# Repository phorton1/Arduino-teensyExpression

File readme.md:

# teensyExpression MIDI controller

This github repository describes and contains the source code and other materials
for a 3D printed, **teensy 3.6** based MIDI controller.  The controller has a 5x5 array
of switches, each with an individually adressable ws2812B colored LED,
four rotary controllers,
a 3.5" touchscreen,
inputs for four (4) standard 1/4" expression pedals, a 1/8" stereo jack used for a serial port, and the main USB type "A" connector,
a USB host port, and, lol, a volt/amp meter to monitor the USB power supply.

*four rotary controllers*

*3.5" touchscreen*

*inputs for four (4) standard 1/4" expression pedals, 1/8" stereo jack for serial port, and the main USB type "A" connector*

*USB host port, and volt/amp meter on USB power supply*

It is intended to be a *foot* controller ... hence the tiered setup which makes it
easier to press buttons with your toes without having to reach over other buttons.
FWIW, I play the guitar barefooted, while sitting in a chair.

There are two major aspects to this project.  First there is the [**hardware**](hardware/), which is
relatively straight forward, and there are circuit diagrams, fusion 360 files, some
instructions, and so on that might allow someone to create a copy if they wanted to.

The second major aspect is the [**software**](design/). Inasmuch as this was conceived as BOTH an
experimental platform to let me mess with USB midi, and particularly the **Fishman FTP
Triple Play** dongle/controller, it also has been programmed to fit into my existing
performance setup.  For me, it is "gig ready", as well as a place I can try different
experiments with various things.

The software does not present itself as a general purpose, commercially viable,
consumer product.  Though that could be done, it is not my primary focus. So, while
I would be able to create, for example, a box on which the end user could map the
buttons to various MIDI CC control messages at "run time", that is not currently
implemented.

Because the entire thing can be (fairly) easily programmed from the Arduino IDE,
at this time I am selfishly doing whatever the heck I want in C++.   Some stuff
has been modularized and incorporated into things like a system configuration "preferences"
page, with persistent values stored in EEPROM, other stuff is "hard coded" into the C++, an
approach which limits the use of this by less technically saavy "consumer" or "nubie"
readers and potential users.

That's what it is.

There is still, in my opinion, considerable value in making this public, and so,
here, in spite of ongoing development, I am creating a public github
repository so that I can present it to you.

## THIS Repository Organization

The following subfolders are considered "public":

* [teensyExpression/](teensyExpression/) - contains the C++ source code,
  including the main INO file (teensyExpression.ino) and the C++ and H files
  needed to build the program.
* [design/](design/) - contains a description of the software architecture,
  with ideas on how other programmers might extend it, along with a
  description of the [User Interface](design/readme_ui.md) in it's
  current incarnation, including the [songMachine](design/readme_songmachine.md)
* [hardware/](hardware/) - contains the basic schematic, circuit diagrams,
  and information about building the electronics portion of the project.
* [ftp/](ftp/) - contains separate discussions and documents regarding
   my reverse engineering efforts on the FTP Triple Play dongle and controller

There are a number of other sub-folders which are considered "private" for my own
personal use, and/or which exist only to support the readme.md files in the this
and the above subfolders:

* **images** - contains images used on this and various readme pages
* **junk** - contains a variety of weird files, images, doc files, that, for me, pertain
      to the design of the project, but which are not meant to be necessrily useful
      for a reader or anyone besides myself.
* **tests** - contains a number of test programs that are not necessarily currently up-to-date
    or useful.  I keep these for posterities sake as they may have snippets of code I will
    need in the future.

### 3D Printing Information

There is a separate repository containing the Fusion 360, STL, and gcode files
for this project that were used to 3D print the box and buttons.

* [fusion/](https://github.com/phorton1/Arduino-teensyExpression-fusion) - contains the STL, fusion 360 files, and notes on how to print and assemble the box

### Please See

This teensyExpression pedal is intimately involved with my long term ongoing
**[rPi bare metal vGuitar rig](https://hackaday.io/project/165696-rpi-bare-metal-vguitar-rig)**
project at hackaday.

In that process I have developed a number of other repositories which might be of interest
to audio system development hackers, including:

* **[circle](https://github.com/phorton1/circle)** - my fork of a a C++ bare metal rPi
development framework
* **[circle-prh](https://github.com/phorton1/circle-prh)** - my extensions to Circle, including
a port of the **Teensy Audio Library** to rPi bare metal, and an Arduino like development
approach.
* **[Loooper](https://github.com/phorton1/circle-prh-apps-Looper)** - a bare metal rPi based **Audio Looper**
including a 3D printed case with a 7" touchscreen, which hooks up to, and is controlled by,
this teensyExpression pedal.

### Notes on Building and GitHub **DEPENDENCIES**

This project relies on the teensyDuino installation.

It also depends on a number of Arduino libraries that must be manually placed in your
Arduino/libraries folder.  There is one small library that I wrote (myDebug.h and myDebug.cpp),
that I generally use in my Arduino programs, and is common to more than one of my published projects.

In addition there are several libraries that are publicly available, but unchanged by me
(ILI9341_t3 and ILI9341_fonts), which I have forked into my github account for ease in finding them,
and to provide me with a stable known "snapshot" of those libraries.

And finally there are some libraries that are publicly available, but to which I
have made modifications to, small or large, in order to get them to work in this project
(Paul's USBHost_t36 and my_LCDWIKI_*).

Each of these libraries is available as a github project here in my account, with a
name that is formatted like "Arduino-libraries-NameOfLibrary".   **These libraries
should be "cloned" or otherwise copied into your Arduino/libraries folder**.  Once
you have done that, you may rename them to remove the "Arduino-libraries" portion,
just leaving the NameOfLibrary portion in the directory structure if you wish.

* [myDebug](https://github.com/phorton1/Arduino-libraries-myDebug) -
   A debugging output library common to my Arduino projects, it contains
   global methods with names like "display" and "display_bytes" which are called
   throughout my code, and which can be turned on or off via defines.

* [base64](https://github.com/phorton1/Arduino-libraries-base64) -
  UNMODIFIED fork of Adam Rudd's https://github.com/adamvr/arduino-base64 repository

* [ILI9341_t3](https://github.com/phorton1/Arduino-libraries-ILI9341_t3) and
  [ILI9341_fonts](https://github.com/phorton1/Arduino-libraries-ILI9341_fonts) -
  These are UNMODIFIED versions of Paul's ILI9341 libraries, forked from
  his repository on 2020-10-03.   My program *may* compile and work with
  more current versions that he makes available at https://github.com/PaulStoffregen/ILI9341_t3
  and https://github.com/PaulStoffregen/ILI9341_fonts, but these forks are
  known to compile and work properly with my code.

* [USBHost_t36](https://github.com/phorton1/Arduino-libraries-USBHost_t36) -
  A slightly MODIFIED version of Paul's USBHost_t36 library, forked
  from https://github.com/PaulStoffregen/USBHost_t36 on 2020-10-03.
  The API was changed to make a few functions virtual and to expose
  a few private variables as "protected".

* [SdFat](https://github.com/phorton1/Arduino-libraries-SdFat) -
  A fork of Bill Greiman's https://github.com/greiman/SdFat with one slight
  modification - to increase BUSY_TIMEOUT_MICROS from 500000 to 1000000,
  which fixed problems I was having opening an SD card on a fresh boot.

* [my_LCDWIKI_GUI](https://github.com/phorton1/Arduino-libraries-my_LCDWIKI_GUI),
  [my_LCDWIKI_KBV](https://github.com/phorton1/Arduino-libraries-my_LCDWIKI_KBV), and
  [my_LCDWIKI_TouchScreen](https://github.com/phorton1/Arduino-libraries-my_LCDWIKI_TouchScreen) -
  These repositories contain the rude and crude port of the LCDWIKI Arduino libraries
  to the Teensy for the cheap touch screen I ended up using.  The touch screen
  is an 8 bit parellel port screen that looks like this:

When I started working on this project, I started off using a different, much
faster and more teensy compatible 2.8" SPI touch screen.  One night I burned it, and
because I did not want to wait 6 weeks for a replacement (I live on a remote
island in the tropics) I was forced to go to a slower speed 8 bit parallel
Arduino touch screen ... which in turn required me to port the LCDWIKI library
for it to the teensy 3.6, which I did.

# Credits

Pretty much everything I do has been tremendously influenced by, and is more or less a direct
result of the work done by **Paul Stoffregen** and his wonderful **teensy** series of MPU boards.

Please visit his website at [prjc.com](https://www.prjc.com) and support him by purchasing teensy
boards and teensy related parts and accessories.    He also has github, hackaday, and facebook pages
that you can find easily on the internet. The man's a giant to me, and has forged important new
ground not only with the boards he makes, but also with the **vast** amount of open source
software he has created, not the least of which includes the ws2812 and ili9431 libraries, but
also his audio library, and well, what can you say ... so much more!

Also thanks to the many folks who have contributed to the [lcdwiki](http://www.lcdwiki.com) project.
Though I can't name them by name, many are the times when I have visited their website and utilized
their code.

That's it!

Thanks for checking this out!

Updated October 2020 - Patrick

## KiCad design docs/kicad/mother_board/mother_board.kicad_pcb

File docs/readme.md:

# teensyExpression MIDI controller

This github repository describes and contains the source code and other materials
for a 3D printed, **teensy 3.6** based MIDI controller.  The controller has a 5x5 array
of switches, each with an individually adressable ws2812B colored LED,
four rotary controllers,
a 3.5" touchscreen,
inputs for four (4) standard 1/4" expression pedals, a 1/8" stereo jack used for a serial port, and the main USB type "A" connector,
a USB host port, and, lol, a volt/amp meter to monitor the USB power supply.

*four rotary controllers*

*3.5" touchscreen*

*inputs for four (4) standard 1/4" expression pedals, 1/8" stereo jack for serial port, and the main USB type "A" connector*

*USB host port, and volt/amp meter on USB power supply*

It is intended to be a *foot* controller ... hence the tiered setup which makes it
easier to press buttons with your toes without having to reach over other buttons.
FWIW, I play the guitar barefooted, while sitting in a chair.

There are two major aspects to this project.  First there is the [**hardware**](hardware.md), which is
relatively straight forward, and there are circuit diagrams, fusion 360 files, some
instructions, and so on that might allow someone to create a copy if they wanted to.

The second major aspect is the [**software**](design.md). Inasmuch as this was conceived as BOTH an
experimental platform to let me mess with USB midi, and particularly the **Fishman FTP
Triple Play** dongle/controller, it also has been programmed to fit into my existing
performance setup.  For me, it is "gig ready", as well as a place I can try different
experiments with various things.

The software does not present itself as a general purpose, commercially viable,
consumer product.  Though that could be done, it is not my primary focus. So, while
I would be able to create, for example, a box on which the end user could map the
buttons to various MIDI CC control messages at "run time", that is not currently
implemented.

Because the entire thing can be (fairly) easily programmed from the Arduino IDE,
at this time I am selfishly doing whatever the heck I want in C++.   Some stuff
has been modularized and incorporated into things like a system configuration "preferences"
page, with persistent values stored in EEPROM, other stuff is "hard coded" into the C++, an
approach which limits the use of this by less technically saavy "consumer" or "nubie"
readers and potential users.

That's what it is.

There is still, in my opinion, considerable value in making this public, and so,
here, in spite of ongoing development, I am creating a public github
repository so that I can present it to you.

## THIS Repository Organization

TODO: rework this whole section

This repository contains the C++ source code,
  including the main INO file (teensyExpression.ino) and the C++ and H files
  needed to build the program.

There are a number of other sub-folders which are considered "private" for my own
personal use, and/or which exist only to support the readme.md files in the this
and the above subfolders:

* **images** - contains images used on this and various readme pages
* **junk** - contains a variety of weird files, images, doc files, that, for me, pertain
      to the design of the project, but which are not meant to be necessrily useful
      for a reader or anyone besides myself.
* **tests** - contains a number of test programs that are not necessarily currently up-to-date
    or useful.  I keep these for posterities sake as they may have snippets of code I will
    need in the future.

### 3D Printing Information

There is a separate repository containing the Fusion 360, STL, and gcode files
for this project that were used to 3D print the box and buttons.

TODO: rework

### Please See

This teensyExpression pedal is intimately involved with my long term ongoing
**[rPi bare metal vGuitar rig](https://hackaday.io/project/165696-rpi-bare-metal-vguitar-rig)**
project at hackaday.

In that process I have developed a number of other repositories which might be of interest
to audio system development hackers, including:

* **[circle](https://github.com/phorton1/circle)** - my fork of a a C++ bare metal rPi
development framework
* **[circle-prh](https://github.com/phorton1/circle-prh)** - my extensions to Circle, including
a port of the **Teensy Audio Library** to rPi bare metal, and an Arduino like development
approach.
* **[Loooper](https://github.com/phorton1/circle-prh-apps-Looper)** - a bare metal rPi based **Audio Looper**
including a 3D printed case with a 7" touchscreen, which hooks up to, and is controlled by,
this teensyExpression pedal.

### Notes on Building and GitHub **DEPENDENCIES**

This project relies on the teensyDuino installation.

It also depends on a number of Arduino libraries that must be manually placed in your
Arduino/libraries folder.  There is one small library that I wrote (myDebug.h and myDebug.cpp),
that I generally use in my Arduino programs, and is common to more than one of my published projects.

In addition there are several libraries that are publicly available, but unchanged by me
(ILI9341_t3 and ILI9341_fonts), which I have forked into my github account for ease in finding them,
and to provide me with a stable known "snapshot" of those libraries.

And finally there are some libraries that are publicly available, but to which I
have made modifications to, small or large, in order to get them to work in this project
(Paul's USBHost_t36 and my_LCDWIKI_*).

Each of these libraries is available as a github project here in my account, with a
name that is formatted like "Arduino-libraries-NameOfLibrary".   **These libraries
should be "cloned" or otherwise copied into your Arduino/libraries folder**.  Once
you have done that, you may rename them to remove the "Arduino-libraries" portion,
just leaving the NameOfLibrary portion in the directory structure if you wish.

* [myDebug](https://github.com/phorton1/Arduino-libraries-myDebug) -
   A debugging output library common to my Arduino projects, it contains
   global methods with names like "display" and "display_bytes" which are called
   throughout my code, and which can be turned on or off via defines.

TODO: cleanup NEEDS vs USES forked libraries

* **base64** -
  UNMODIFIED fork of Adam Rudd's https://github.com/adamvr/arduino-base64 repository
* [ILI9341_t3](https://github.com/phorton1/Arduino-libraries-ILI9341_t3) and
  [ILI9341_fonts](https://github.com/phorton1/Arduino-libraries-ILI9341_fonts) -
  These are UNMODIFIED versions of Paul's ILI9341 libraries, forked from
  his repository on 2020-10-03.   My program *may* compile and work with
  more current versions that he makes available at https://github.com/PaulStoffregen/ILI9341_t3
  and https://github.com/PaulStoffregen/ILI9341_fonts, but these forks are
  known to compile and work properly with my code.

* [USBHost_t36](https://github.com/phorton1/Arduino-libraries-USBHost_t36) -
  A slightly MODIFIED version of Paul's USBHost_t36 library, forked
  from https://github.com/PaulStoffregen/USBHost_t36 on 2020-10-03.
  The API was changed to make a few functions virtual and to expose
  a few private variables as "protected".

* [SdFat](https://github.com/phorton1/Arduino-libraries-SdFat) -
  A fork of Bill Greiman's https://github.com/greiman/SdFat with one slight
  modification - to increase BUSY_TIMEOUT_MICROS from 500000 to 1000000,
  which fixed problems I was having opening an SD card on a fresh boot.

* [my_LCDWIKI_GUI](https://github.com/phorton1/Arduino-libraries-my_LCDWIKI_GUI),
  [my_LCDWIKI_KBV](https://github.com/phorton1/Arduino-libraries-my_LCDWIKI_KBV), and
  [my_LCDWIKI_TouchScreen](https://github.com/phorton1/Arduino-libraries-my_LCDWIKI_TouchScreen) -
  These repositories contain the rude and crude port of the LCDWIKI Arduino libraries
  to the Teensy for the cheap touch screen I ended up using.  The touch screen
  is an 8 bit parellel port screen that looks like this:

When I started working on this project, I started off using a different, much
faster and more teensy compatible 2.8" SPI touch screen.  One night I burned it, and
because I did not want to wait 6 weeks for a replacement (I live on a remote
island in the tropics) I was forced to go to a slower speed 8 bit parallel
Arduino touch screen ... which in turn required me to port the LCDWIKI library
for it to the teensy 3.6, which I did.

# Credits

Pretty much everything I do has been tremendously influenced by, and is more or less a direct
result of the work done by **Paul Stoffregen** and his wonderful **teensy** series of MPU boards.

Please visit his website at [prjc.com](https://www.prjc.com) and support him by purchasing teensy
boards and teensy related parts and accessories.    He also has github, hackaday, and facebook pages
that you can find easily on the internet. The man's a giant to me, and has forged important new
ground not only with the boards he makes, but also with the **vast** amount of open source
software he has created, not the least of which includes the ws2812 and ili9431 libraries, but
also his audio library, and well, what can you say ... so much more!

Also thanks to the many folks who have contributed to the [lcdwiki](http://www.lcdwiki.com) project.
Though I can't name them by name, many are the times when I have visited their website and utilized
their code.

That's it!

Thanks for checking this out!

Updated October 2020 - Patrick

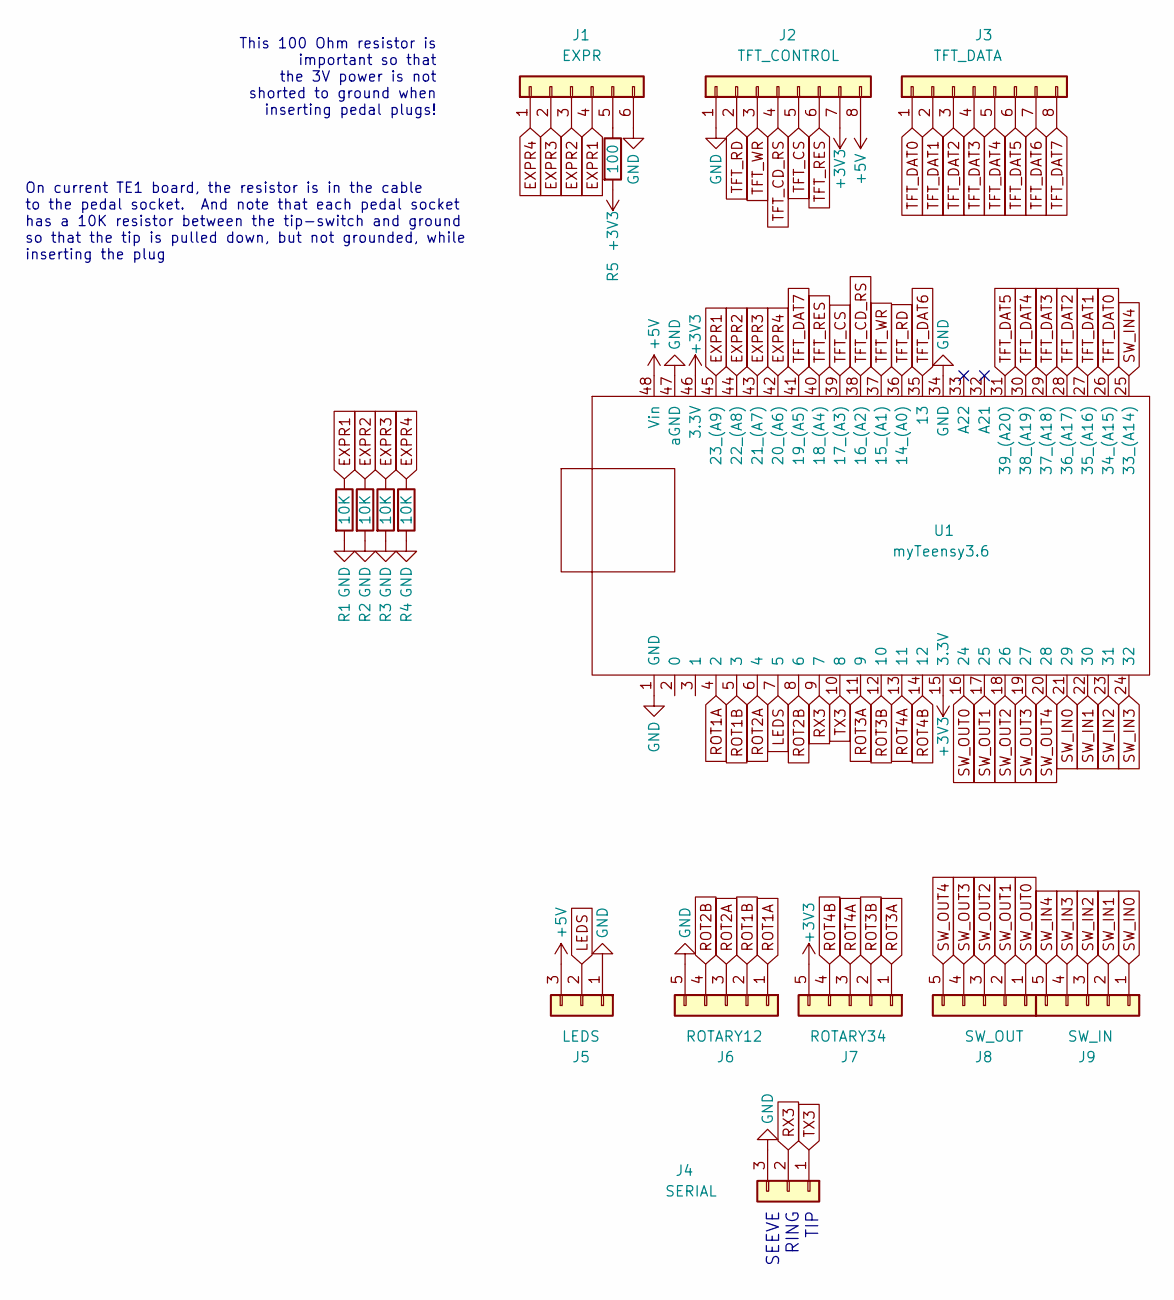
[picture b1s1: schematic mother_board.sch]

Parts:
J1: EXPR; myPinSocket_1x06
J2: TFT_CONTROL; myJSTx08
J3: TFT_DATA; myJSTx08
J4: SERIAL; myPinSocket_1x03
J5: LEDS; myPinSocket_1x03
J6: ROTARY12; myPinSocket_1x05
J7: ROTARY34; myPinSocket_1x05
J8: SW_OUT; myPinSocket_1x05
J9: SW_IN; myPinSocket_1x05
R1, R2, R3, R4: 10K; myResistor
R5: 100; myResistor
U1: myTeensy3.6

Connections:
+3V3: J2.7, J7.5, R5.2, U1.15 (3.3V), U1.46 (3.3V)
+5V: J2.8, J5.3, U1.48 (Vin)
EXPR1: J1.4, R1.1, U1.45 (23_(A9))
EXPR2: J1.3, R2.1, U1.44 (22_(A8))
EXPR3: J1.2, R3.1, U1.43 (21_(A7))
EXPR4: J1.1, R4.1, U1.42 (20_(A6))
GND: J1.6, J2.1, J4.3, J5.1, J6.5, R1.2, R2.2, R3.2, R4.2, U1.1 (GND), U1.34 (GND), U1.47 (aGND)
LEDS: J5.2, U1.7 (5)
unnamed: J1.5, R5.1
ROT1A: J6.1, U1.4 (2)
ROT1B: J6.2, U1.5 (3)
ROT2A: J6.3, U1.6 (4)
ROT2B: J6.4, U1.8 (6)
ROT3A: J7.1, U1.11 (9)
ROT3B: J7.2, U1.12 (10)
ROT4A: J7.3, U1.13 (11)
ROT4B: J7.4, U1.14 (12)
RX3: J4.2, U1.9 (7)
SW_IN0: J9.1, U1.21 (29)
SW_IN1: J9.2, U1.22 (30)
SW_IN2: J9.3, U1.23 (31)
SW_IN3: J9.4, U1.24 (32)
SW_IN4: J9.5, U1.25 (33_(A14))
SW_OUT0: J8.1, U1.16 (24)
SW_OUT1: J8.2, U1.17 (25)
SW_OUT2: J8.3, U1.18 (26)
SW_OUT3: J8.4, U1.19 (27)
SW_OUT4: J8.5, U1.20 (28)
TFT_CD_RS: J2.4, U1.38 (16_(A2))
TFT_CS: J2.5, U1.39 (17_(A3))
TFT_DAT0: J3.1, U1.26 (34_(A15))
TFT_DAT1: J3.2, U1.27 (35_(A16))
TFT_DAT2: J3.3, U1.28 (36_(A17))
TFT_DAT3: J3.4, U1.29 (37_(A18))
TFT_DAT4: J3.5, U1.30 (38_(A19))
TFT_DAT5: J3.6, U1.31 (39_(A20))
TFT_DAT6: J3.7, U1.35 (13)
TFT_DAT7: J3.8, U1.41 (19_(A5))
TFT_RD: J2.2, U1.36 (14_(A0))
TFT_RES: J2.6, U1.40 (18_(A4))
TFT_WR: J2.3, U1.37 (15_(A1))
TX3: J4.1, U1.10 (8)

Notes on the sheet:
SEEVE RING TIP
This 100 Ohm resistor is important so that the 3V power is not shorted to ground when inserting pedal plugs!
On current TE1 board, the resistor is in the cable to the pedal socket. And note that each pedal socket has a 10K resistor between the tip-switch and ground so that the tip is pulled down, but not grounded, while inserting the plug

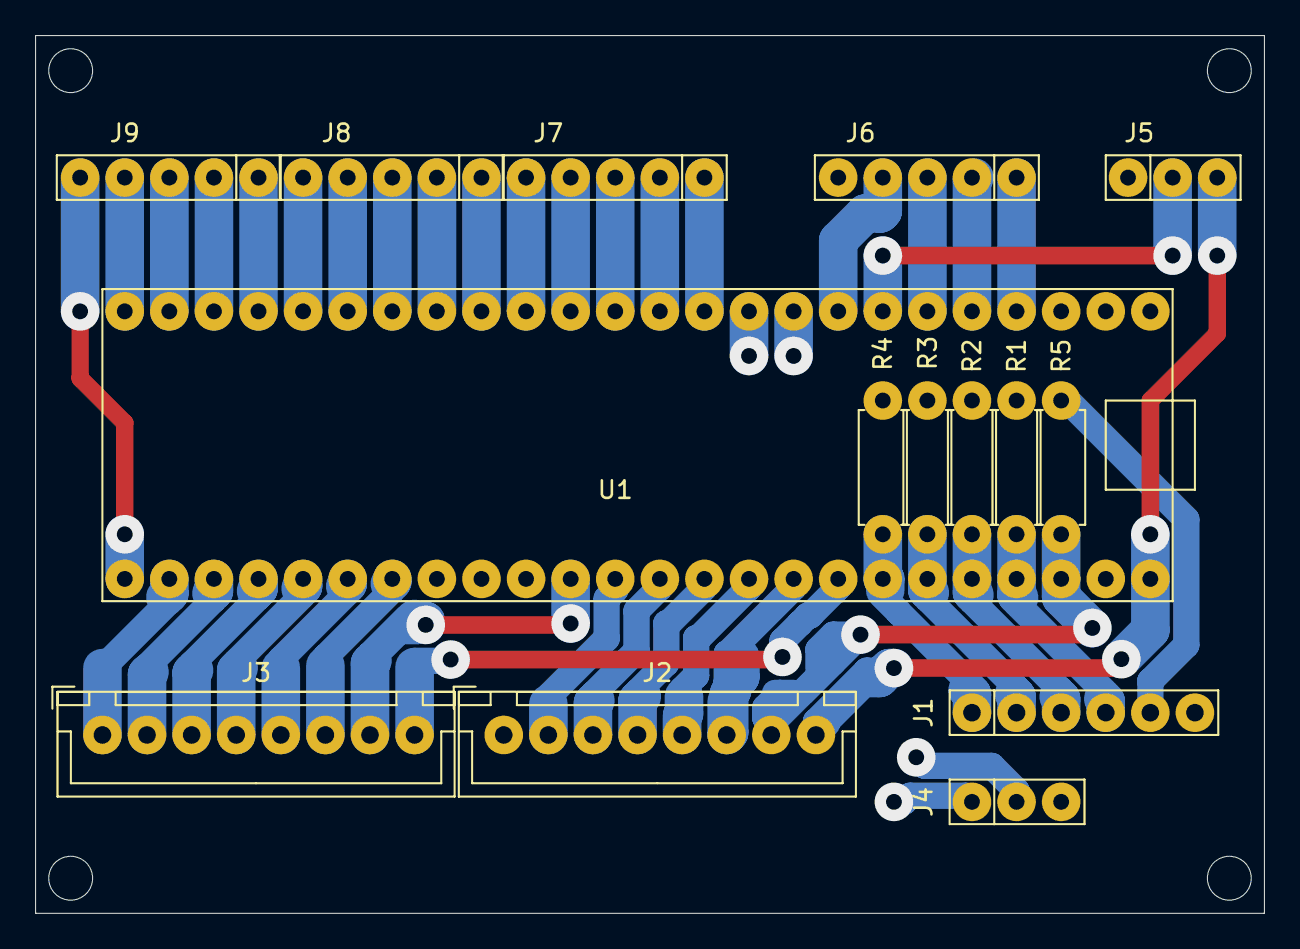
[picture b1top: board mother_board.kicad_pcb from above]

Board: 2 copper layers, 70.0 x 50.0 mm, 15 parts (0 on the bottom side), 42 nets.

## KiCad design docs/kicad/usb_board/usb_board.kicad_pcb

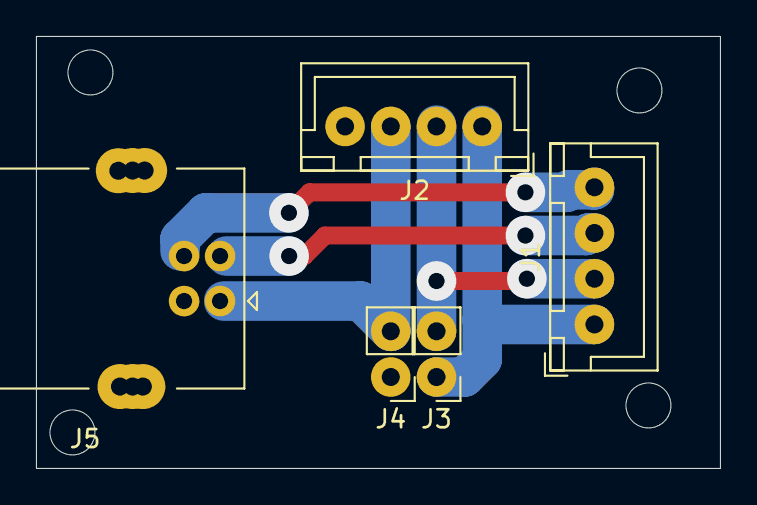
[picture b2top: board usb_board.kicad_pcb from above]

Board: 2 copper layers, 38.0 x 24.0 mm, 5 parts (0 on the bottom side), 6 nets.

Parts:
J1: USB_OUT; myJSTx04
J2: PWR_IO; myJSTx04
J3: JUMP_OUT; myPinHeader_1x02
J4: JUMP_IN; myPinHeader_1x02
J5: myUSB_B_Socket

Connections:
+5V: J2.3, J4.2, J5.1
D+: J1.4, J5.3
D-: J1.3, J5.2
GND: J2.4, J4.1, J5.4
unnamed: J1.1, J2.1, J3.1
unnamed: J1.2, J2.2, J3.2

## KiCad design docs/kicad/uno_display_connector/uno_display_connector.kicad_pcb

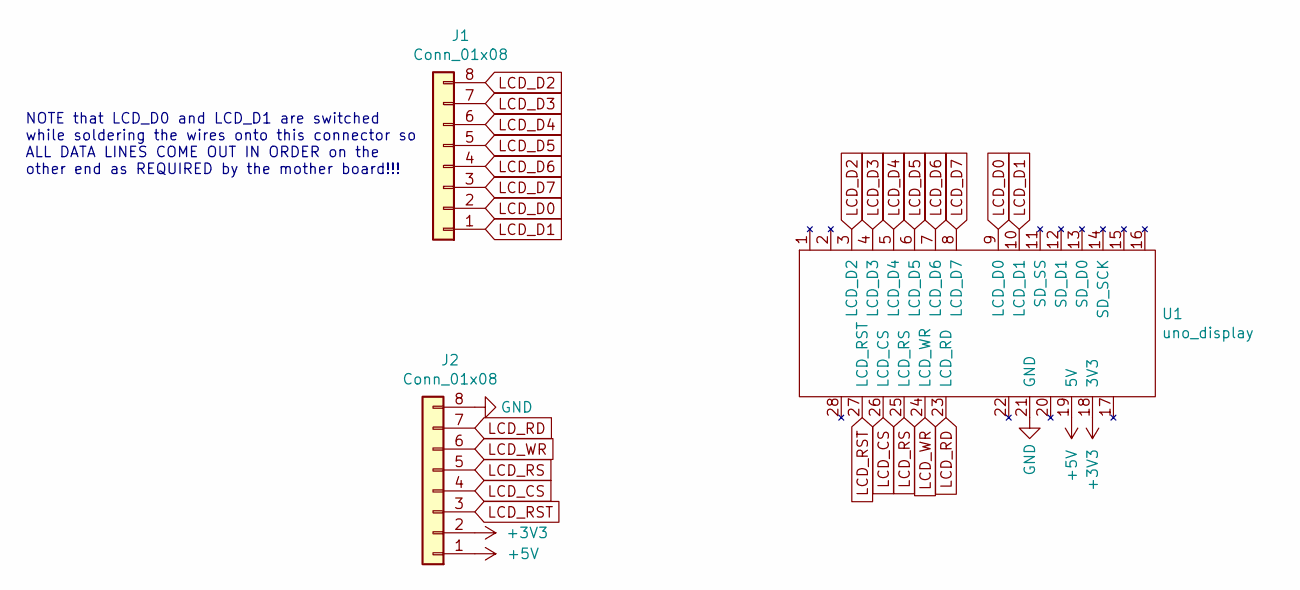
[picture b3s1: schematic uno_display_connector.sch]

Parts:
J1, J2: Conn_01x08; my8Pin
U1: uno_display; unoDisplay

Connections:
+3V3: J2.2, U1.18 (3V3)
+5V: J2.1, U1.19 (5V)
GND: J2.8, U1.21 (GND)
LCD_CS: J2.4, U1.26 (LCD_CS)
LCD_D0: J1.2, U1.9 (LCD_D0)
LCD_D1: J1.1, U1.10 (LCD_D1)
LCD_D2: J1.8, U1.3 (LCD_D2)
LCD_D3: J1.7, U1.4 (LCD_D3)
LCD_D4: J1.6, U1.5 (LCD_D4)
LCD_D5: J1.5, U1.6 (LCD_D5)
LCD_D6: J1.4, U1.7 (LCD_D6)
LCD_D7: J1.3, U1.8 (LCD_D7)
LCD_RD: J2.7, U1.23 (LCD_RD)
LCD_RS: J2.5, U1.25 (LCD_RS)
LCD_RST: J2.3, U1.27 (LCD_RST)
LCD_WR: J2.6, U1.24 (LCD_WR)

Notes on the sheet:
NOTE that LCD_D0 and LCD_D1 are switched while soldering the wires onto this connector so ALL DATA LINES COME OUT IN ORDER on the other end as REQUIRED by the mother board!!!

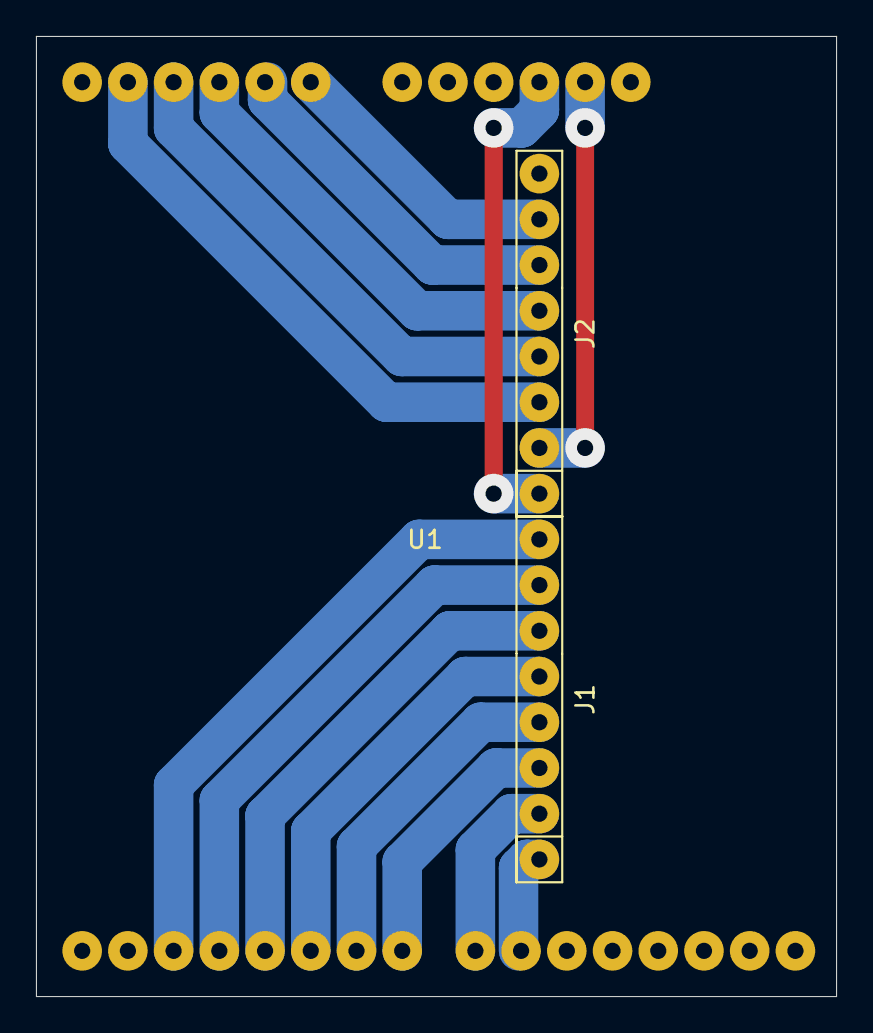
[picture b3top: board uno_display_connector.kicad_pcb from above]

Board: 2 copper layers, 44.5 x 53.3 mm, 3 parts (0 on the bottom side), 16 nets.

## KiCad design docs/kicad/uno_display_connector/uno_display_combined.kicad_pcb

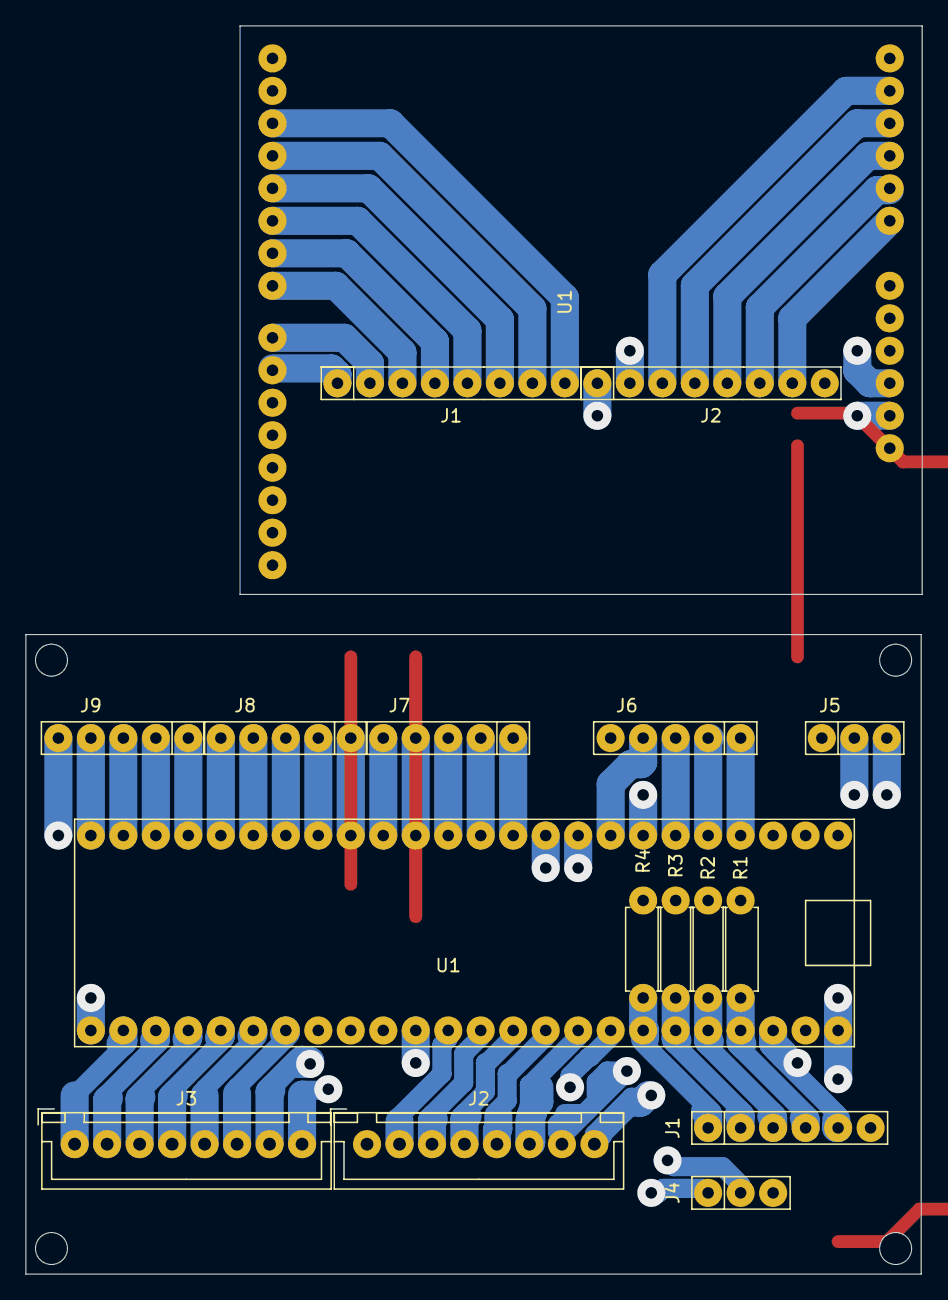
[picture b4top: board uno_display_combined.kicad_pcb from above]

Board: 2 copper layers, 70.0 x 50.0 mm, 17 parts (0 on the bottom side), 55 nets.

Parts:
J1: EXPR; myPinSocket_1x06
J1#2, J2: Conn_01x08; my8Pin
J2#2: TFT_CONTROL; myJSTx08
J3: TFT_DATA; myJSTx08
J4: SERIAL; myPinSocket_1x03
J5: LEDS; myPinSocket_1x03
J6: ROTARY12; myPinSocket_1x05
J7: ROTARY34; myPinSocket_1x05
J8: SW_OUT; myPinSocket_1x05
J9: SW_IN; myPinSocket_1x05
R1, R2, R3, R4: 10K; myResistor
U1: uno_display; unoDisplay
U1#2: myTeensy3.6

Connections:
+3V3: J1.5, J2.1, J2#2.7, J7.5, U1.18, U1#2.15, U1#2.46
+5V: J2.2, J2#2.8, J5.3, U1.19, U1#2.48
EXPR1: J1.4, R1.1, U1#2.45
EXPR2: J1.3, R2.1, U1#2.44
EXPR3: J1.2, R3.1, U1#2.43
EXPR4: J1.1, R4.1, U1#2.42
GND: J1.6, J2.8, J2#2.1, J4.3, J5.1, J6.5, R1.2, R2.2, R3.2, R4.2, U1.21, U1#2.1, U1#2.34, U1#2.47
LCD_CS: J2.4, U1.26
LCD_D0: J1#2.2, U1.9
LCD_D1: J1#2.1, U1.10
LCD_D2: J1#2.8, U1.3
LCD_D3: J1#2.7, U1.4
LCD_D4: J1#2.6, U1.5
LCD_D5: J1#2.5, U1.6
LCD_D6: J1#2.4, U1.7
LCD_D7: J1#2.3, U1.8
LCD_RD: J2.7, U1.23
LCD_RS: J2.5, U1.25
LCD_RST: J2.3, U1.27
LCD_WR: J2.6, U1.24
LEDS: J5.2, U1#2.7
unnamed: U1.2, U1#2.2
ROT1A: J6.1, U1#2.4
ROT1B: J6.2, U1#2.5
ROT2A: J6.3, U1#2.6
ROT2B: J6.4, U1#2.8
ROT3A: J7.1, U1#2.11
ROT3B: J7.2, U1#2.12
ROT4A: J7.3, U1#2.13
ROT4B: J7.4, U1#2.14
RX3: J4.2, U1#2.9
SW_IN0: J9.1, U1#2.21
SW_IN1: J9.2, U1#2.22
SW_IN2: J9.3, U1#2.23
SW_IN3: J9.4, U1#2.24
SW_IN4: J9.5, U1#2.25
SW_OUT0: J8.1, U1#2.16
SW_OUT1: J8.2, U1#2.17
SW_OUT2: J8.3, U1#2.18
SW_OUT3: J8.4, U1#2.19
SW_OUT4: J8.5, U1#2.20
TFT_CD_RS: J2#2.4, U1#2.38
TFT_CS: J2#2.5, U1#2.39
TFT_DAT0: J3.1, U1#2.26
TFT_DAT1: J3.2, U1#2.27
TFT_DAT2: J3.3, U1#2.28
TFT_DAT3: J3.4, U1#2.29
TFT_DAT4: J3.5, U1#2.30
TFT_DAT5: J3.6, U1#2.31
TFT_DAT6: J3.7, U1#2.35
TFT_DAT7: J3.8, U1#2.41
TFT_RD: J2#2.2, U1#2.36
TFT_RES: J2#2.6, U1#2.40
TFT_WR: J2#2.3, U1#2.37
TX3: J4.1, U1#2.10

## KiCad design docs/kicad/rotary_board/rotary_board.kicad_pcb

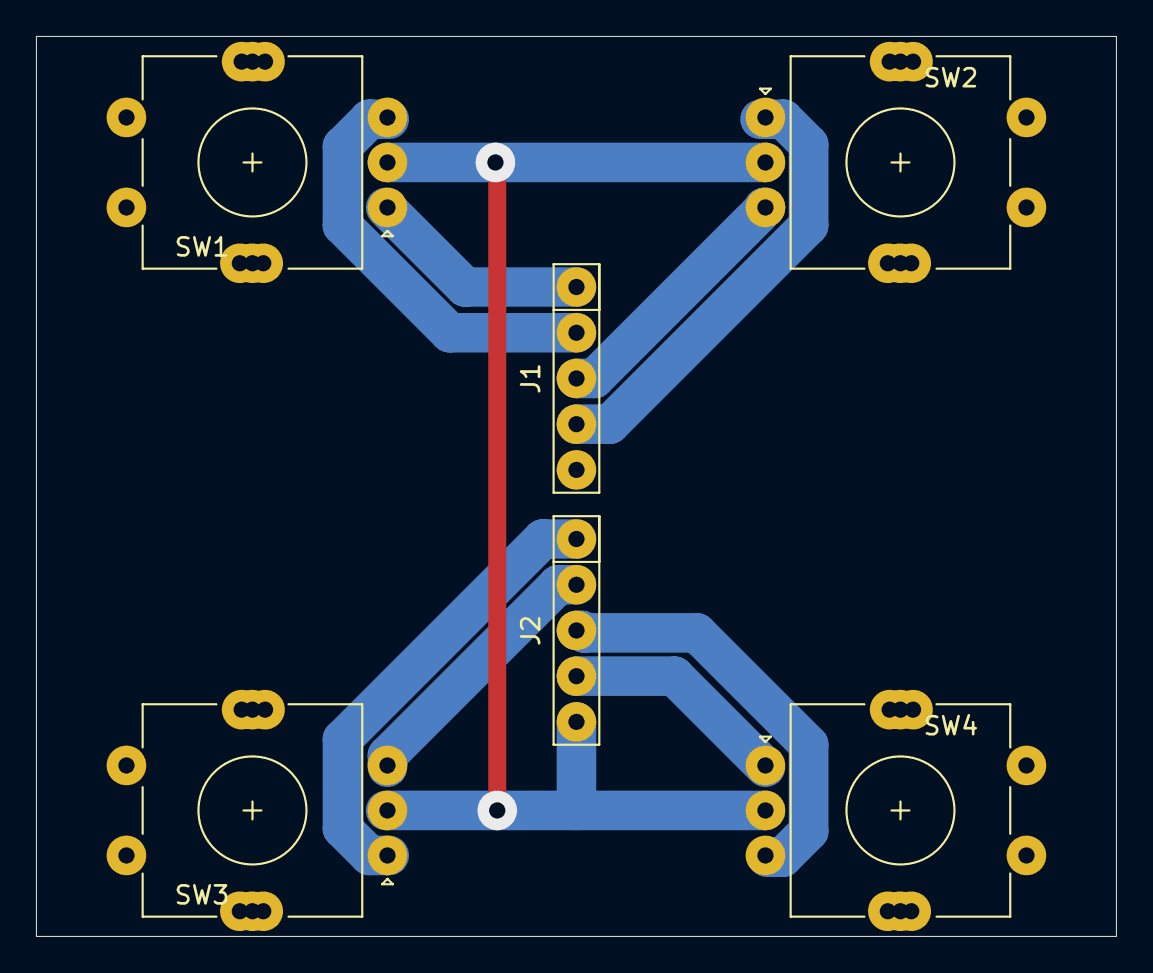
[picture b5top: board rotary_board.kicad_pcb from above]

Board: 2 copper layers, 60.0 x 50.0 mm, 6 parts (0 on the bottom side), 10 nets.

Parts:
J1: ROTARY12; my5Pin
J2: ROTARY34; my5Pin
SW1, SW2, SW3, SW4: Rotary_Encoder_Switch; myRotaryEncoder

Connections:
+3V3: J2.5, SW1.C, SW2.C, SW3.C, SW4.C
GND: J1.5, SW1.S1, SW1.S2, SW2.S1, SW2.S2, SW3.S1, SW3.S2, SW4.S1, SW4.S2
ROT1A: J1.1, SW1.A
ROT1B: J1.2, SW1.B
ROT2A: J1.4, SW2.A
ROT2B: J1.3, SW2.B
ROT3A: J2.1, SW3.A
ROT3B: J2.2, SW3.B
ROT4A: J2.4, SW4.A
ROT4B: J2.3, SW4.B

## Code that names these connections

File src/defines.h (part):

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// expression pedal plugs, resulting in an effective range of
// about 0..(0.75 * 1023)

#define PIN_EXPR4    20     // pin1 A6
#define PIN_EXPR3    21     // pin2 A7
#define PIN_EXPR2    22     // pin3 A8
#define PIN_EXPR1    23     // pin4 A9
                            // pin5 3.3V
                            // pin6 GND

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// The TFT controls and power are on the 2nd front 8 pin JST connector, facing
//
// GND              			// pin 1
#define TFT_RD     		14      // pin 2
#define TFT_WR          15 		// pin 3
#define TFT_CD_RS		16 		// pin 4
#define TFT_CS          17 		// pin 5
#define TFT_RESET       18 		// pin 6
// 5V               			// pin 7
// 3.3V             			// pin 8

// Touch Screen Redefinitions

#define YP  TFT_CD_RS   // 16=A2        // A2 maps to LCD_RS on arduino    // must be an analog pin, use "An" notation!
#define XM  TFT_CS      // 17=A3        // A3 maps to LCD_CS on arduino    // must be an analog pin, use "An" notation!
#define YM  TFT_DATA0   // 34=A15        / 8  maps to LCD_D0 on arduino    // can be a digital pin
#define XP  TFT_DATA1   // 35=A16       // 9  maps to LCD_D1 on arduino    // can be a digital pin



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
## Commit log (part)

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2020-05-16 added teensyExpression controller
2020-05-25 Work in progress (has primitive tests of LEDS, BUTTONS, and SCREEN)s
2020-05-26 sanity checkin
2020-05-29 CLEANUP ACTUAL SYSTEM ... and then sanity checkin while trying to get USB Host integated
2020-05-30 WORKING BUT BUSTED SCREEN - added Serial2 to teensyPi and Serial3 to Expression Pedal
2020-05-31 added CHEAP_TFT to project
2020-05-31 renamed ili9431 and LCD stuff to "my" - cosmetic changes to teeensyExpression
2020-06-01 clean up and checkin befoore trying rotary controls
2020-06-07 HARDWARE COMPLETE
2020-06-07 PIN ASSIGNMENTS RESOLVED - created expressionPedals.h & cpp
2020-06-07 a little cleanup - removed "m_loop_event_cleared" kludge, added room in rawButton m_event_state to replace it on the lookout for the anomoly that made me kludge it in the first place
2020-06-07 turned on MIDI_HOST
2020-06-08 get rid of old files
2020-06-08 basic initial oldRigConfig UI
2020-06-09 INITIAL CURVES Broke out systemConfig into it's own source files. Added experimental "rotary brightness curve" Created preliminary "curve" editor
2020-06-10 initial system configuration
2020-06-11 better scheme for config editor terminal nodes; added config::end() method
2020-06-11 playing around with FTP sysex
2020-06-12 working on FTP host mode ... general cleanup too.
2020-06-13 cleaned up architecture - closer but not there yet
2020-06-15 FINALLY FIGURED OUT FTP - SPOOF AND STRING SENSITIVITY
2020-06-16 FTP POLY/MONO MODE IMPORTANT DOCUMENT
2020-06-16 onMidiHostEvent is supposed to be virtual
2020-06-16 MIDI HOST DIRECT INTERRUPT PASS THROUGH I need some time to think about how to proceed from here. - try to spoof FTP editor again? - try to measure event timing and see if I can play the guitar with 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
2020-06-16 comments only
2020-06-16 CRUDE BUT WORKING FTP MIDI HOST - spoofs the Windows FTP Editor !!!
2020-06-16 adding denormalized copy of teensyDuino file to my project
2020-06-16 effing checking in head with unresolved issues
2020-06-16 comments
2020-06-16 adding usb_desc to my project
2020-06-16 added configuration option
2020-06-16 comments and debugging only
2020-06-17 broke out FTP.h and CPP - minor changes *need to generally cleanup and remove incorrect myAsserts*
2020-06-17 checkin before starting FTP tuner/sensititify UI
2020-06-18 add handling for first FTP commands and replies
2020-06-18 cleanup
2020-06-19 IN FLUX - also changed USBHost_t36.h again ...
2020-06-19 pretty good working initFTPIfNeeded() - starting to move to a window (vs configuration) metaphor. Thinking about overall architecture.
2020-06-19 clean up h-file includes
2020-06-19 moved to "design"
2020-06-20 preliminary sensitivity editor
2020-06-20 saving off dlgFtpSens
2020-06-20 reworked BUTTON handling ... now includes LEDs (colors) and repeat funcitonality
2020-06-21 start FTP_MIDI_SPEC
2020-06-21 got rid of WITH_XXX defines moved midi_host_on and init() to myMidiHost
2020-06-21 changed dbgSerial to a pointer to a Stream allow for diverting output from myDebug to other hardware serial devices on teensy
2020-06-22 breif cleanup of design notes
2020-06-22 massaging towards what I want 1 ...
2020-06-23 implemented LCDWIKI_KBV::dim() which is basically not fast enough to use note that I have ili9486 SPI modules (from rPi) but don't know if they will be faster even if I get Paul's DMA stuff to work w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
2020-06-23 scrollable options allow for more patches than config shows
2020-06-23 moved my stuff to LCDWIKI_GUI_prh.cpp added param to printJustified replaced LCDWIKI_GUI::text_mode with m_use_bc cleaned up comments
2020-06-23 implemented modal windows and m_flags on expWindow added param to expWindow::begin() for coming down the stack added yesNoDialog and used it in configSystem FactoryReset touched all printJustified() 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
2020-06-23 made global patch system button that calls ftpTuner <--> ftpSensitivity as modal dialogs
2020-06-23 PATCHES ARE RESPONSIBLE FOR SAVING BUTTON STATE in end() if they are going to use it to store data!
2020-06-24 added isEnabled() to options
2020-06-25 proof of concept - FTP on remote device tested with MidiOx routing
2020-06-25 defined basic PREFS
2020-06-25 revisit button handling
2020-06-25 add my outgoing events to midi monitor
2020-06-25 still talking
2020-06-26 allow for null dbgSerial port
2020-06-26 implement serialPortOption to direct output to one port or the other
2020-06-26 basic pref-based config options scheme
2020-06-26 CONFIG DIALOGS - implemented test terminal node dialog windows
2020-06-27 implement4ed winConfigPedal
2020-06-27 changed patch names slightly
2020-06-27 CONFIG_PEDALS - added CALIBRATION, MIN and MAX value x offsets better overall display
2020-06-27 added blue dot to CONFIG PEDAL
2020-06-27 removed a blank line
2020-06-27 minor fix - resuse max and strings for PREF_PATCH_NUM *may* rework the way I cache prefs and restore them when aborting from dialogs withing configuration ...
2020-06-27 rework config menu, at FTP parent and PREF_FTP_PORT
2020-06-27 implement PREF_FTP_PORT, cleanup monitor display a bit
2020-06-28 added initial midi monitor prefs
2020-06-28 created winFTPSettings - prepare for PREF FILTER
2020-06-28 basic splits and performance filter
2020-06-28 added midi activity indicators
2020-06-30 FTP Checksum and patch display, Standard Midi CCs, more FTP/analysis begin newRig design.
2020-06-30 implement mySendFtpSysex, fix some midiActivity indicators
2020-06-30 added defines for new rig
2020-06-30 tempo explorations
2020-07-12 moved tests to subdirectories (finally have subdiretories in /src/Arduino!)
2020-07-13 Final initial "SET PEDAL POSTION" algorithm. velocityTest sucks. PIDTest sort of works. See notes in PIDTest.
2020-07-14 AFTER DEBUGGING PEDAL CIRCUIT BOARD NEED TO CHANGE EXPR BOX PEDAL CIRCUITS!! so there is a 1K resistor on the power, and the rest are just switches to ground.
2020-07-15 test integration with autoPedal
2020-07-19 dont send battery check command if there's no FTP port
2020-07-19 AUTO_PEDAL basic intergration into teensyExpression
2020-07-20 test newRig - don't like it, esp vol curves in AudioBus ...
2020-07-20 slightly better detent
2020-07-27 reverse engineer TowerPro MG955 servo board
2020-07-27 formalized tempo getting
2020-08-02 got rid of patchNewRig
2020-08-13 FRAMEWORK FOR LOOPER RELATIVE VOLUMES and MONO_MODE SYNTH volumes also moved ftp_poly and bend modes to ftp.cpp and got rid of fast button to ftp tuner/sensitivity
2020-09-14 add medium empty circuit board
2020-09-19 FIRST INTEGRATED LOOPER AND TEENSY-EXPRESSION TEST Here on the teensyExpression and teensyPi side teensyPi now recognizes my "midi packets" coming in over the Serial2 port from the teensyExpression, 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
2020-09-25 more comments
2020-09-25 fixed proof-of-cooncept loop pedal volume serial output to rPi
2020-09-27 WIP - INTEGRATED LOOPER 1.0
2020-09-27 WIP - INTEGRATED LOOPER 1.0 - basic buttons and functionality
2020-09-29 introduced commonDefines.h
2020-09-30 reworked patchNewRig to remove dependency on button state
2020-10-03 fix old rig non-serial loop pedal
2020-10-03 RESTRUCTURE FOR GOING PUBLIC - removed my old teensyExpression "ftp_analysis" folder - added previous "public" design folders - created myDebugPrivate for non-public stuff
2020-10-03 testing commits
2020-10-03 test change
2020-10-03 made fusion into separate repository
2020-10-03 separate repository for teensyExpression fusion files
2020-10-03 better wording
2020-10-03 one more change
2020-10-03 added USBHost_t36 description
2020-10-03 denormalized commonDefines.h
2020-10-06 added preference for FILE SYSTEM PORT
2020-10-06 added RENAME to file server
2020-10-08 improved remote fileSystem recv_file performance
2020-10-08 prep for songMachine
2020-10-09 TERMINOLOGY - RIGS: changed what I call top level windows from 'patches' to RIGS
2020-10-10 Initial checkin of songParser (sanity checkin)
2020-10-10 final prep to write song machine
2020-10-10 initial working songMachine
2020-10-11 fixed Serial3 fileSystem communications
2020-10-11 songs need to be moved to separate repository
2020-10-12 Added and implemented LOOP_COMMAND_SET_LOOP .. GIG READY PROOF OF CONCEPT
2020-10-13 song language extensions: CALLs to METHODs, FLASHING, display colors, UI
2020-10-13 individualized global #defines
2020-10-13 cleaned up BUTTONS (no more groups, radios, or intimate use of state) cleaned up H files - got rid of oldRig, changed newRig to LooperRig added rigBase for use by songMachine fixed minor bugs due to 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
2020-10-14 comments and cleanup
2020-10-14 abstracted songMachine Loop Commands to rigBase
2020-10-14 2nd PROOF OF CONCEPT (Beta Candidate) quick_mode leaves other buttons (col4 and row4) active added ABORT_RECORDING to long click ERASE_TRACK added winFTPTuner & swapModal winFTPSensitivity to short c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
2020-10-14 got rid of obs files
2020-10-19 tuning up rig - new sampletank organization
2020-10-20 allow for - and . in identifiers
2020-10-21 moved source to teensyExpression subfolder
2020-10-21 updating readme files
2020-10-21 just want plain text
2020-10-21 minor readme changes
2020-10-22 added example code
2020-10-22 proofreading changes
2020-10-23 minor readme change
2020-10-24 added china cat (not working)
2020-11-08 fixed crude search for buttons ...
2021-03-15 2021-03-15 Cleanup
2022-09-12 REBUILT and deployed
2023-08-04 restructure - move source to /src
2023-08-04 restructure - move songs to /data/songs
2023-08-04 docs - add new fusion .f3z design
2023-08-04 docs - restructure
2023-08-04 docs - add new fusion STL exports and prusa 3MF files
2023-08-04 Fixed #elser, added TEENSY_EXPRESSION_VERSION to startup display and config "System" menu item
2023-08-08 minor debugging changes
2023-08-20 docs/kicad - added new display_connector, reworked tentative new PCB
2023-08-20 start MAKE NEW motherboard and display_connector FOR olds TeensyExprssion box with TE2 code
2023-08-21 BUILD new combined mother_board and uno_display_connector. PRINT new display_frame.
2023-08-22 AFTER BUILD NEW PCBs - corrected display connector pins; removed old combined plot and gcode file
2023-08-23 added 1K resistor to pedal power to keep from crashing while inserting plugs
2023-08-24 fixed compiler warnings from new teensyDuino 1.58
2023-08-24 updated AutoPedal comments only
2023-08-24 updated preferences.txt
2023-08-25 EEPROM - check/write 237 to EEPROM 0 to identify teensyExpression1 and automatically reset prefs if not
2023-09-04 updated to Looper v2.11 commonDefines.h
2023-10-10 added LICENSE.TXT and empty docs/readme.md to most public repositories
2023-10-10 got rid of Arduino-libraries-myDebugPrivate, moved teensyExpression/examples to Arduino/autoPedal
2023-11-02 fix broken links across all repos with introduction of base-apps-gitUI::repoDocs.pm
2024-05-13 update all TE preferences.txt to build in /src/ArduinoBuilds for easier clean builds
2025-01-12 convert teensyExpression1 to myLCD library & remove LCD_WIKI stuff - also moved test programs out of teensyExpression2
2025-01-14 final changes for redrawn, reprinted, and rebuilt teensyExpression box (teensyExpressionRedraw.f3z)
2025-01-14 got fileClient/console/budy working with TE1 - quite a few changes - totally changed expSystem.cpp::handleSerialData() with copy of code from TE2 - use #define SERIAL_DEVICE Serial3 insead of "Serial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
2025-01-14 temporary setting of default debug device to USB for new TE box testing and turned down fileSystem debugging
2025-01-14 Manually normalized fileXXXX.cpp & h files between TE1 and TE2 in prep for some bug-fix rework ...
2025-01-16 completly reworked COMMON TE1 and TE2 fileXXXX h and cpp and mem_check.cpp files
2025-01-17 recommit unsaved rotary_board.pc ...
2025-01-17 remove superflous "testing" debug message from rigLooper::begin()
2025-01-20 notes regarding resistors for pedals
2025-01-20 OBJECT MODEL CHANGE - got rid of rigBase.h, rigtTest.cpp & h, rigMidiHost.cpp & H, Quantiloop references, Auto Pedal references; change not complete big simplification with static rig_looper, config_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
2025-01-21 rework button task(); add re-entrancy protection & simplify debouncing
2025-01-21 fix some pedal bugs & cleanup debugging - FIRST SUCCESFUL INTEGRATION TEST
2025-01-22 trim rigDefs.h (equivilant to iPadDefines.h in TE2, but that has info on other devices in comments)
